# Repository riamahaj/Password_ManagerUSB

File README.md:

# Password_ManagerUSB
This repository is for our ECE 411 Password Manager Bank project
It features a MicroSD card reader, an OLED for displaying password websites, and a keypad for scrolling and selecting passwords to output. 
It has 32GB space for extra storage and has encryption features, as well as a webpage that displays websites and passwords with a password strength indicator.

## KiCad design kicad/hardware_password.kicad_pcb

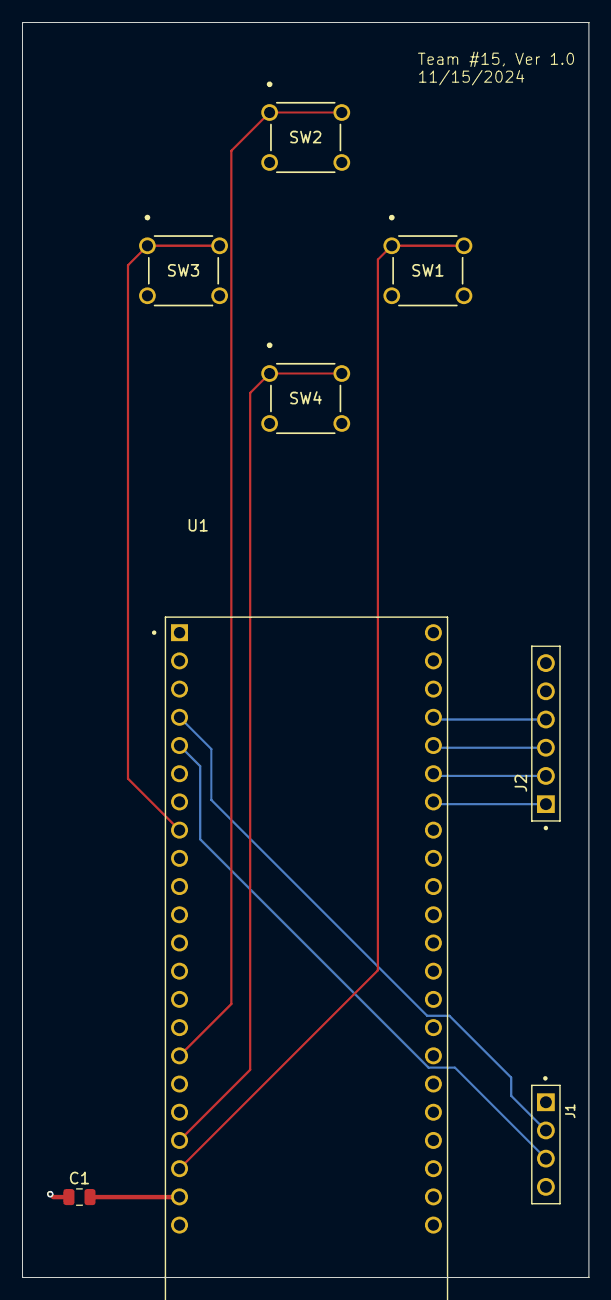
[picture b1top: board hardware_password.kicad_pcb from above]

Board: 4 copper layers, 51.0 x 113.0 mm, 8 parts (0 on the bottom side), 13 nets.

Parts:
C1: 100pF, 0.1nF; C_0805_2012Metric
J1: Conn_01x04_Socket; SULLINS_PPTC041LFBN-RC
J2: Conn_01x06_Socket; SULLINS_PPTC061LFBN-RC
SW1, SW2, SW3, SW4: B3F-1020; SW_B3F-1000_OMR
U1: ESP32-S3-DEVKITC-1-N8R2; XCVR_ESP32-S3-DEVKITC-1-N8R2

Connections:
/5V: C1.2, J1.1, J2.5, U1.J1_21 (5V0)
/CS: J2.1, U1.J3_7 (MTDI/GPIO41)
/IO10: SW2.1, SW2.2, U1.J1_16 (GPIO10)
/IO13: SW4.1, SW4.2, U1.J1_19 (GPIO13)
/IO14: SW1.1, SW1.2, U1.J1_20 (GPIO14)
/IO15: SW3.1, SW3.2, U1.J1_8 (GPIO15)
/MISO: J2.4, U1.J3_4 (GPIO1)
/MOSI: J2.3, U1.J3_5 (GPIO2)
/SCK: J2.2, U1.J3_6 (MTMS/GPIO42)
/SCL: J1.3, U1.J1_5 (GPIO5)
/SDA: J1.2, U1.J1_4 (GPIO4)
GND: C1.1, J1.4, J2.6, SW1.3, SW1.4, SW2.3, SW2.4, SW3.3, SW3.4, SW4.3, SW4.4, U1.J1_22 (GND), U1.J3_1 (GND), U1.J3_21 (GND), U1.J3_22 (GND)
unnamed: U1.J1_1 (3V3), U1.J1_2 (3V3)

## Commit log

2024-11-07 Create kicad
2024-11-07 Project Schedule
2024-11-14 Create block digram folder
2024-11-15 Added decryption/encryption
    Features to be added:
    security measure to unlock device
    way to add passwords to csv file
2024-11-19 moved power planes to inner layers
2024-12-13 Update 411-code.ino
    My added code is encased in comment lines in case it breaks stuff
2024-12-13 Update 411-code.ino
    Added library and new 'strength' field
2024-12-13 random csv generator + web server with strength indicator
2024-12-13 case CAD
